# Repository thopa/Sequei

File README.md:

# Sequei
Arduino analog pot controlled drum machine based on the concept of Mutable Instrument's Anushri and Grids drum sequencer.

Features:

4 trigger drum Channels with Density and X Y drum mapping (see Mutable Instruments Grids)
Clock Sync
Control Voltage over Map X and Map Y

Special thanks to:
Olivier Gillet (olivier@mutable-instruments.net)
Honza Hrubes /aka ashimoke ashimoke@gmail.com
Geert @ http://Goltstein.nl
Darwin Grosse @  (www.20objects.com).

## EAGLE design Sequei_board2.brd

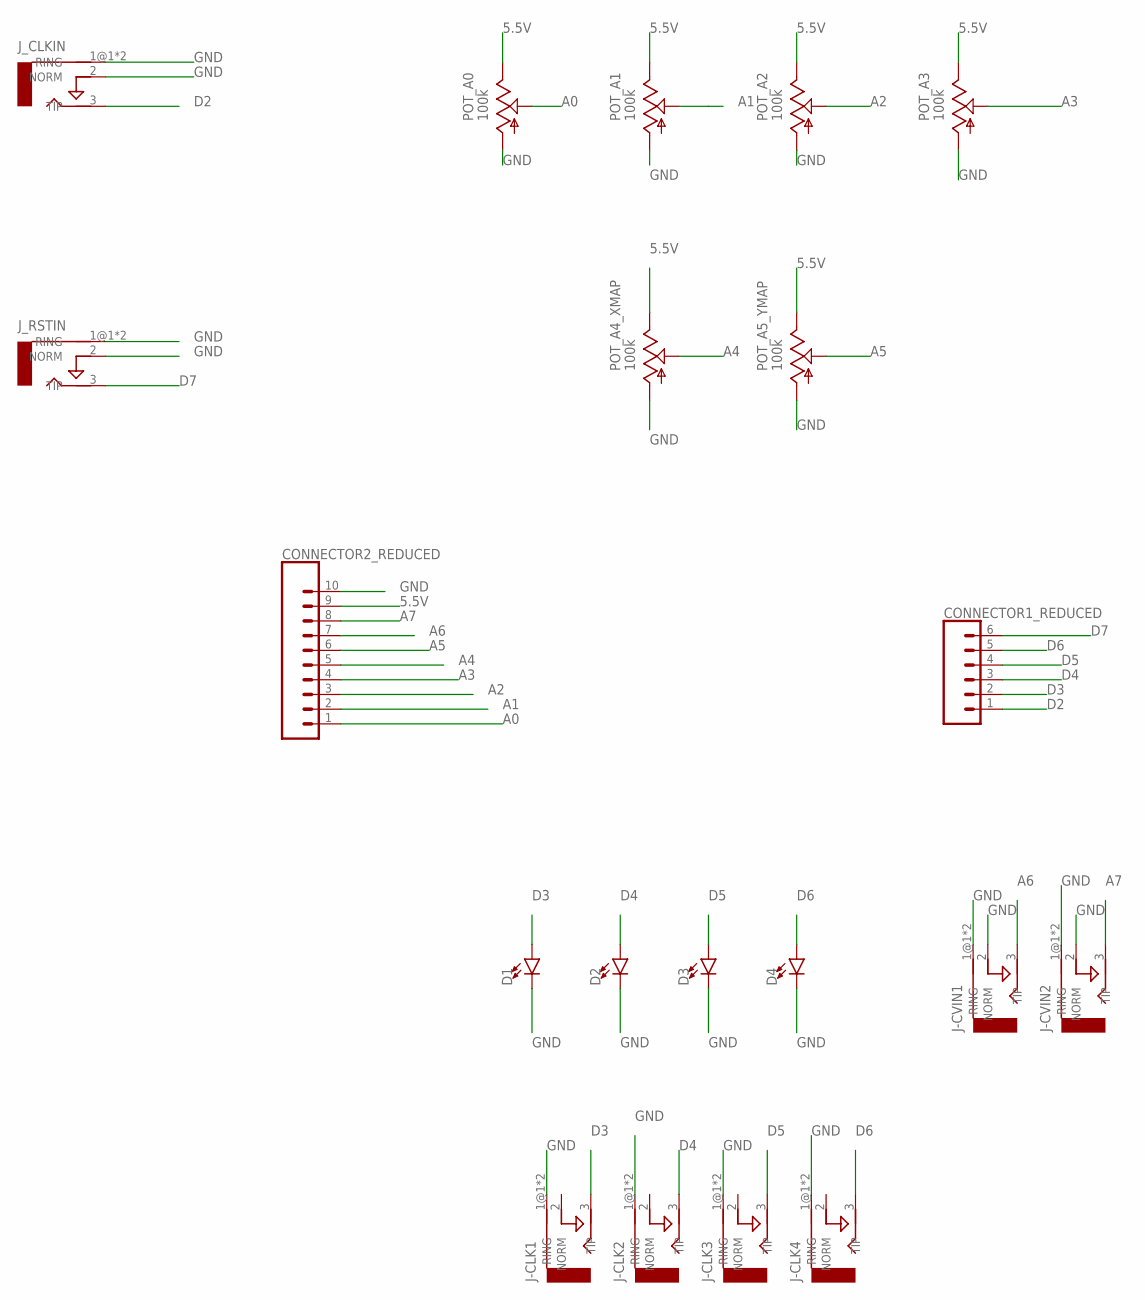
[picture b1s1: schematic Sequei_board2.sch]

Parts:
CONNECTOR1_REDUCED: CONN_06LONGPADS; 1X06_LONGPADS
CONNECTOR2_REDUCED: CONN_10_LONGPADS10_LONGPADS; 1X10_LONGPADS
D1, D2, D3, D4: LED-3MM-NO_SILK; LED_3MM-NS
J-CLK1, J-CLK2, J-CLK3, J-CLK4: AUDIO-JACKERTHENVAR; ERTHENVAR-JACK
J-CVIN1, J-CVIN2: AUDIO-JACKERTHENVAR; ERTHENVAR-JACK
J_CLKIN: AUDIO-JACKERTHENVAR; ERTHENVAR-JACK
J_RSTIN: AUDIO-JACKERTHENVAR; ERTHENVAR-JACK
POT_A0, POT_A1, POT_A2, POT_A3, POT_A4_XMAP, POT_A5_YMAP: 100k; 9MM_SNAP-IN_POT

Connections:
5.5V: CONNECTOR2_REDUCED.9, POT_A0.3 (E), POT_A1.3 (E), POT_A2.3 (E), POT_A3.3 (E), POT_A4_XMAP.3 (E), POT_A5_YMAP.3 (E)
A0: CONNECTOR2_REDUCED.1, POT_A0.2 (S)
A1: CONNECTOR2_REDUCED.2, POT_A1.2 (S)
A2: CONNECTOR2_REDUCED.3, POT_A2.2 (S)
A3: CONNECTOR2_REDUCED.4, POT_A3.2 (S)
A4: CONNECTOR2_REDUCED.5, POT_A4_XMAP.2 (S)
A5: CONNECTOR2_REDUCED.6, POT_A5_YMAP.2 (S)
A6: CONNECTOR2_REDUCED.7, J-CVIN1.3 (TIP)
A7: CONNECTOR2_REDUCED.8, J-CVIN2.3 (TIP)
D2: CONNECTOR1_REDUCED.1, J_CLKIN.3 (TIP)
D3: CONNECTOR1_REDUCED.2, D1.A, J-CLK1.3 (TIP)
D4: CONNECTOR1_REDUCED.3, D2.A, J-CLK2.3 (TIP)
D5: CONNECTOR1_REDUCED.4, D3.A, J-CLK3.3 (TIP)
D6: CONNECTOR1_REDUCED.5, D4.A, J-CLK4.3 (TIP)
D7: CONNECTOR1_REDUCED.6, J_RSTIN.3 (TIP)
GND: CONNECTOR2_REDUCED.10, D1.K (C), D2.K (C), D3.K (C), D4.K (C), J-CLK1.1@1 (RING), J-CLK1.1@2 (RING), J-CLK2.1@1 (RING), J-CLK2.1@2 (RING), J-CLK3.1@1 (RING), J-CLK3.1@2 (RING), J-CLK4.1@1 (RING), J-CLK4.1@2 (RING), J-CVIN1.1@1 (RING), J-CVIN1.1@2 (RING), J-CVIN1.2 (NORM), J-CVIN2.1@1 (RING), J-CVIN2.1@2 (RING), J-CVIN2.2 (NORM), J_CLKIN.1@1 (RING), J_CLKIN.1@2 (RING), J_CLKIN.2 (NORM), J_RSTIN.1@1 (RING), J_RSTIN.1@2 (RING), J_RSTIN.2 (NORM), POT_A0.1 (A), POT_A1.1 (A), POT_A2.1 (A), POT_A3.1 (A), POT_A4_XMAP.1 (A), POT_A5_YMAP.1 (A)

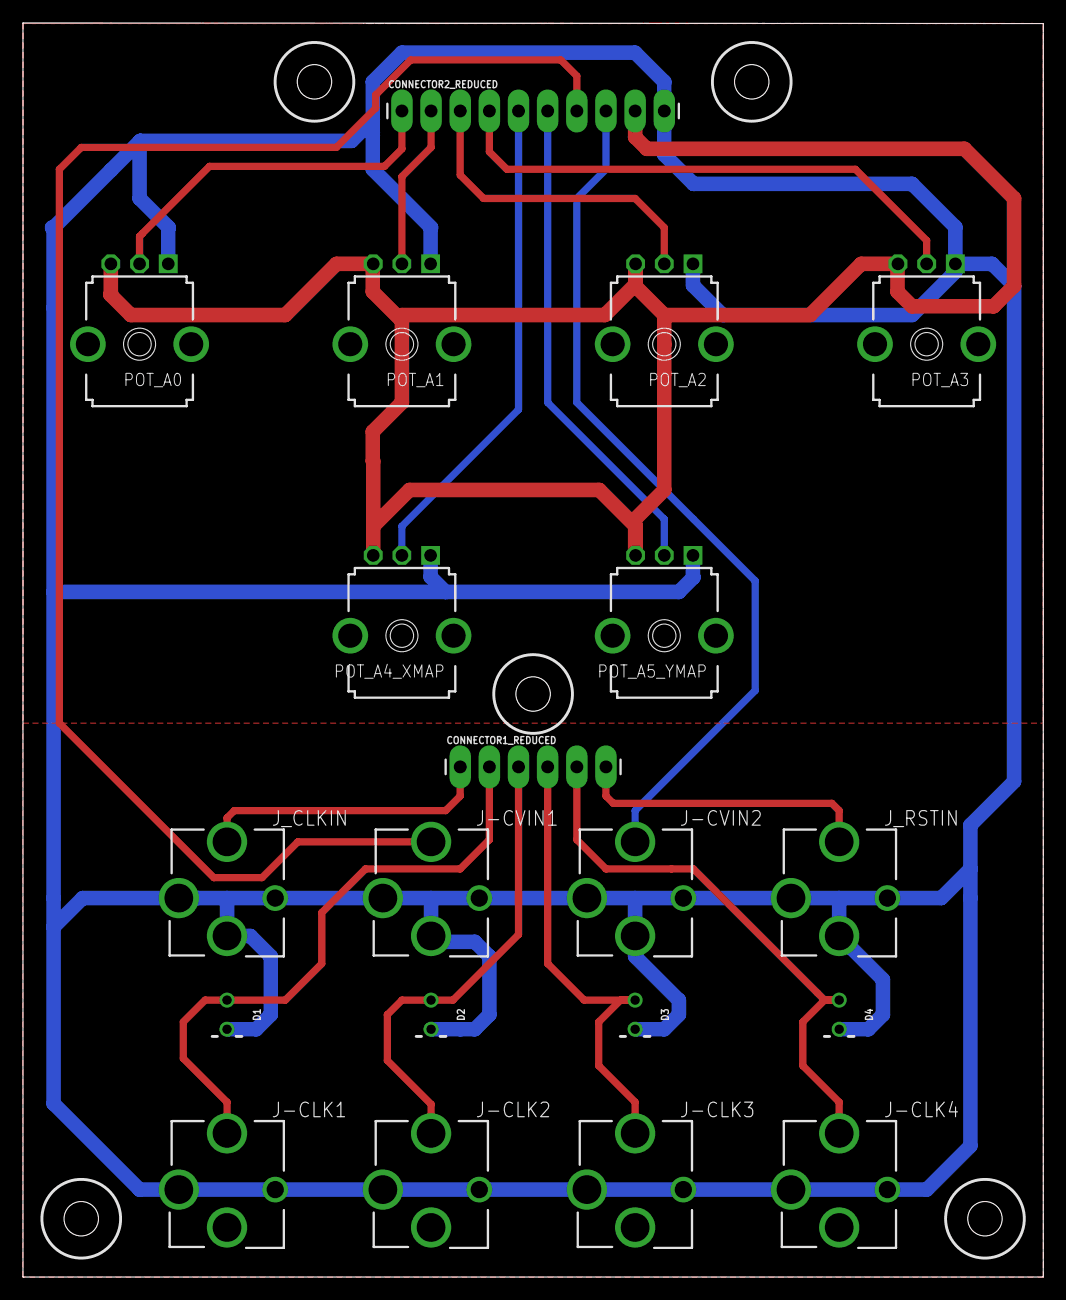
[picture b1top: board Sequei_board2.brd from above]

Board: 2 copper layers, 88.9 x 109.3 mm, 25 parts (0 on the bottom side), 16 nets.

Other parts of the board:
H1, H2, H3, H4, H5: DRIL-3

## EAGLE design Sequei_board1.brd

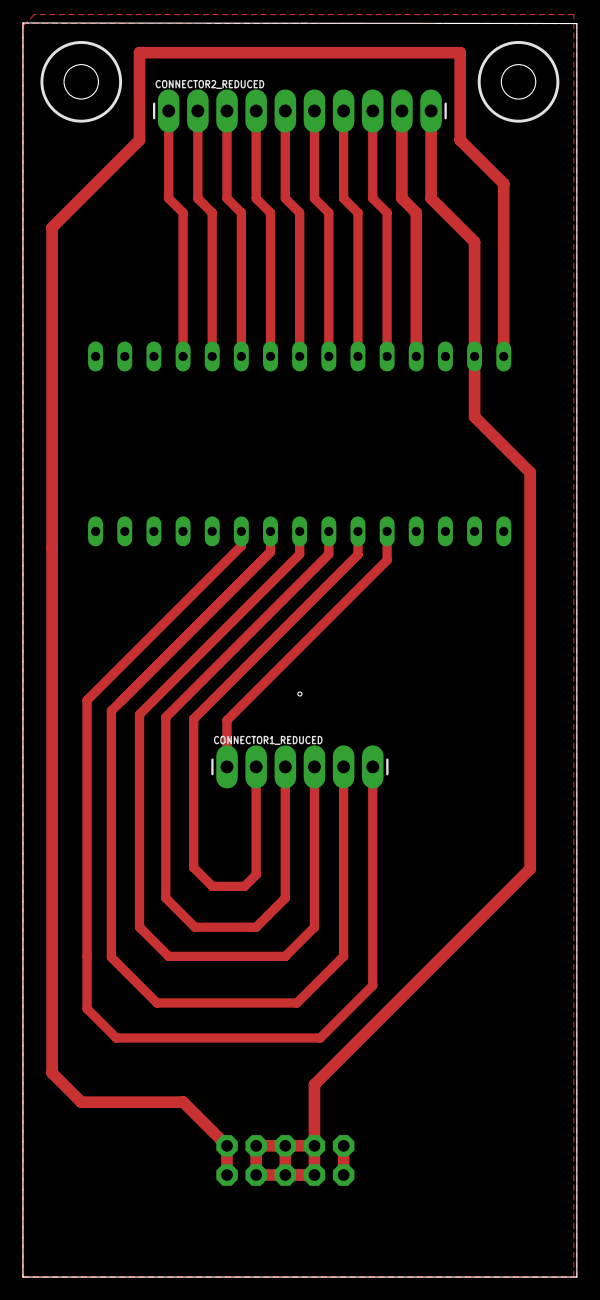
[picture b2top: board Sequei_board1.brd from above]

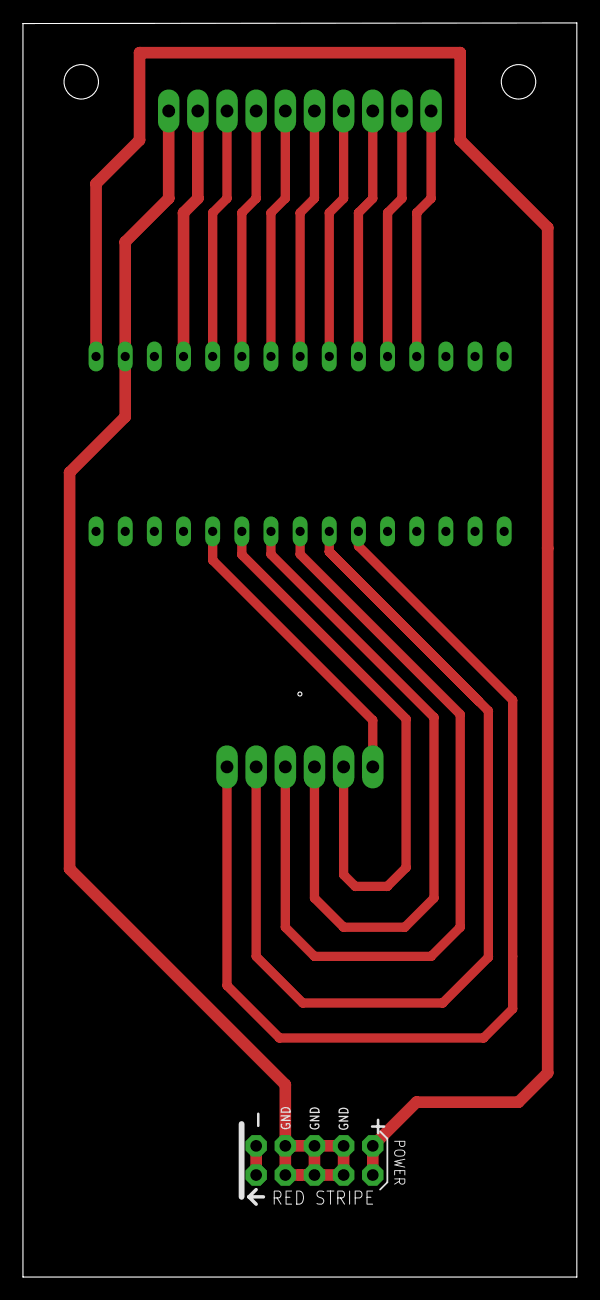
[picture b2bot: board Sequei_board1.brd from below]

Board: 2 copper layers, 48.3 x 109.3 mm, 6 parts (2 on the bottom side), 18 nets.

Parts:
CONNECTOR1_REDUCED: 1X06_LONGPADS
CONNECTOR2_REDUCED: 1X10_LONGPADS
H1, H2: DRIL-3
SV1: EURO_POWER_HEADERFAT_PADS; EURO_PWR_HEADER_FAT
U$1: NANO

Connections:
5.5V: CONNECTOR2_REDUCED.9, U$1.5V
-12V: SV1.1, SV1.2
A0: CONNECTOR2_REDUCED.1, U$1.A0
A1: CONNECTOR2_REDUCED.2, U$1.A1
A2: CONNECTOR2_REDUCED.3, U$1.A2
A3: CONNECTOR2_REDUCED.4, U$1.A3
A4: CONNECTOR2_REDUCED.5, U$1.A4
A5: CONNECTOR2_REDUCED.6, U$1.A5
A6: CONNECTOR2_REDUCED.7, U$1.A6
A7: CONNECTOR2_REDUCED.8, U$1.A7
D2: CONNECTOR1_REDUCED.1, U$1.D2
D3: CONNECTOR1_REDUCED.2, U$1.D3
D4: CONNECTOR1_REDUCED.3, U$1.D4
D5: CONNECTOR1_REDUCED.4, U$1.D5
D6: CONNECTOR1_REDUCED.5, U$1.D6
D7: CONNECTOR1_REDUCED.6, U$1.D7
GND: CONNECTOR2_REDUCED.10, SV1.3, SV1.4, SV1.5, SV1.6, SV1.7, SV1.8, U$1.GND
VCC: SV1.9, SV1.10, U$1.RAW

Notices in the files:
parts and their libraries:
SparkFun-Connectors: Licensing: Creative Commons ShareAlike 4.0 International - https://creativecommons.org/licenses/by-sa/4.0
